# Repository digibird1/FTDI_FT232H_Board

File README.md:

FTDI_FT232H_Board
=================

PCB design for the FT232H USB 2.0 conroler chip. 
The design connects to the GPIO of the Altera DE0  FPGA board

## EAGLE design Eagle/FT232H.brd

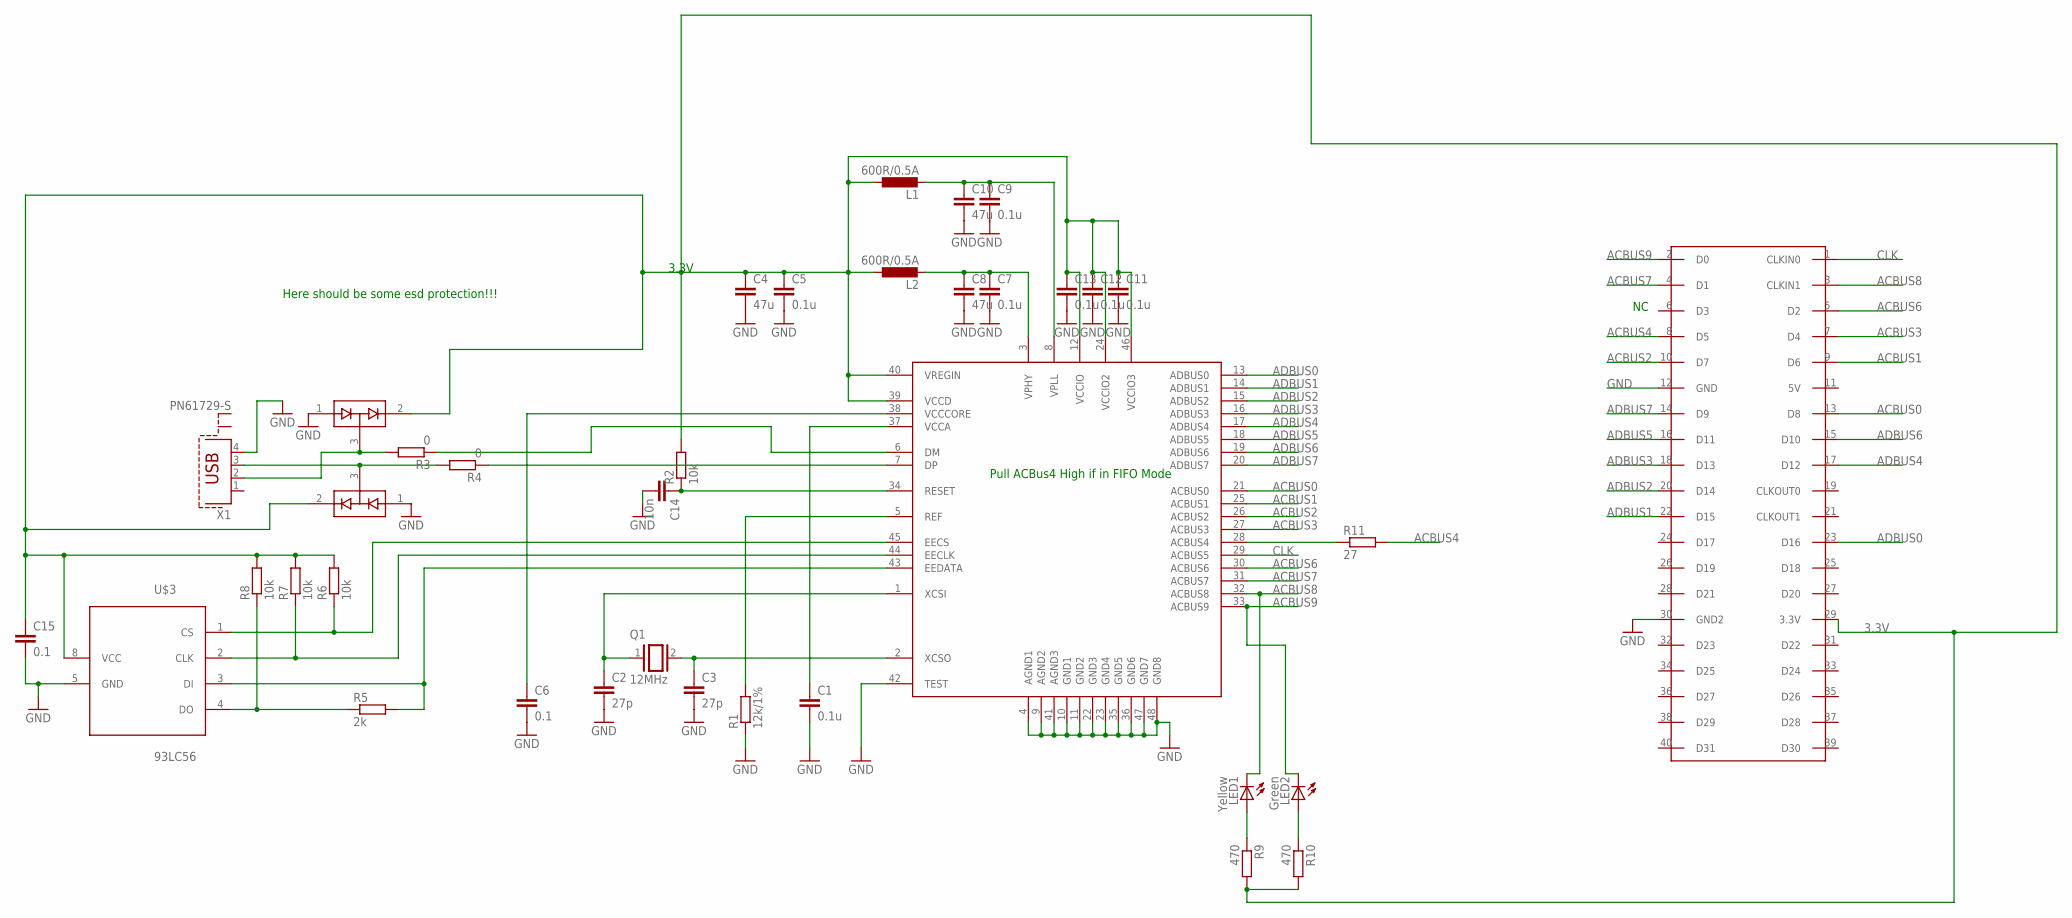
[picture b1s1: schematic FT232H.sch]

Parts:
C1, C5, C7, C9, C11, C12, C13: 0.1u; C0805
C2, C3: 27p; C0805
C4, C8, C10: 47u; C0805
C6, C15: 0.1; C0805
C14: 10n; C0805
D1, D2: BAV99; SOT23
L1, L2: 600R/0.5A; R0805
LED1: Yellow; R0805
LED2: Green; R0805
Q1: 12MHz; QS
R1: 12k/1%; M0805
R2, R6, R7, R8: 10k; M0805
R3, R4: 0; M0805
R5: 2k; M0805
R9, R10: 470; M0805
R11: 27; M0805
U$1: FT232H; LQFP48
U$2: FPGA_GPIO_DE0; 2X20
U$3: 93LC56; DIL-08
X1: PN61729-S

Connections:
3.3V: C4.1, C5.1, C11.1, C12.1, C13.1, C15.1, D1.2 (C2), D2.2 (C2), L1.1, L2.1, R2.2, R6.2, R7.2, R8.2, R9.2, R10.2, U$1.12 (VCCIO), U$1.24 (VCCIO2), U$1.39 (VCCD), U$1.40 (VREGIN), U$1.46 (VCCIO3), U$2.29 (3.3V), U$3.8 (VCC)
ACBUS0: U$1.21 (ACBUS0), U$2.13 (D8)
ACBUS1: U$1.25 (ACBUS1), U$2.9 (D6)
ACBUS2: U$1.26 (ACBUS2), U$2.10 (D7)
ACBUS3: U$1.27 (ACBUS3), U$2.7 (D4)
ACBUS4: R11.2, U$2.8 (D5)
ACBUS6: U$1.30 (ACBUS6), U$2.5 (D2)
ACBUS7: U$1.31 (ACBUS7), U$2.4 (D1)
ACBUS8: LED1.2 (C), U$1.32 (ACBUS8), U$2.3 (CLKIN1)
ACBUS9: LED2.2 (C), U$1.33 (ACBUS9), U$2.2 (D0)
ADBUS0: U$1.13 (ADBUS0), U$2.23 (D16)
ADBUS1: U$1.14 (ADBUS1), U$2.22 (D15)
ADBUS2: U$1.15 (ADBUS2), U$2.20 (D14)
ADBUS3: U$1.16 (ADBUS3), U$2.18 (D13)
ADBUS4: U$1.17 (ADBUS4), U$2.17 (D12)
ADBUS5: U$1.18 (ADBUS5), U$2.16 (D11)
ADBUS6: U$1.19 (ADBUS6), U$2.15 (D10)
ADBUS7: U$1.20 (ADBUS7), U$2.14 (D9)
CLK: U$1.29 (ACBUS5), U$2.1 (CLKIN0)
GND: C1.2, C2.2, C3.2, C4.2, C5.2, C6.2, C7.2, C8.2, C9.2, C10.2, C11.2, C12.2, C13.2, C14.2, C15.2, D1.1 (A1), D2.1 (A1), R1.1, U$1.4 (AGND1), U$1.9 (AGND2), U$1.10 (GND1), U$1.11 (GND2), U$1.22 (GND3), U$1.23 (GND4), U$1.35 (GND5), U$1.36 (GND6), U$1.41 (AGND3), U$1.42 (TEST), U$1.47 (GND7), U$1.48 (GND8), U$2.12 (GND), U$2.30 (GND2), U$3.5 (GND), X1.4
unnamed: C9.1, C10.1, L1.2, U$1.8 (VPLL)
unnamed: C1.1, U$1.37 (VCCA)
unnamed: R1.2, U$1.5 (REF)
unnamed: C6.1, U$1.38 (VCCCORE)
unnamed: C2.1, Q1.1, U$1.1 (XCSI)
unnamed: C3.1, Q1.2, U$1.2 (XCSO)
unnamed: C14.1, R2.1, U$1.34 (RESET)
unnamed: R4.1, U$1.7 (DP)
unnamed: D1.3 (COM), R3.2, X1.2
unnamed: R3.1, U$1.6 (DM)
unnamed: C7.1, C8.1, L2.2, U$1.3 (VPHY)
unnamed: D2.3 (COM), R4.2, X1.3
unnamed: R6.1, U$1.45 (EECS), U$3.1 (CS)
unnamed: R7.1, U$1.44 (EECLK), U$3.2 (CLK)
unnamed: R5.2, U$1.43 (EEDATA), U$3.3 (DI)
unnamed: R5.1, R8.1, U$3.4 (DO)
unnamed: LED1.1 (A), R9.1
unnamed: LED2.1 (A), R10.1
unnamed: R11.1, U$1.28 (ACBUS4)

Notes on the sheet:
3.3V
Here should be some esd protection!!!
Pull ACBus4 High if in FIFO Mode

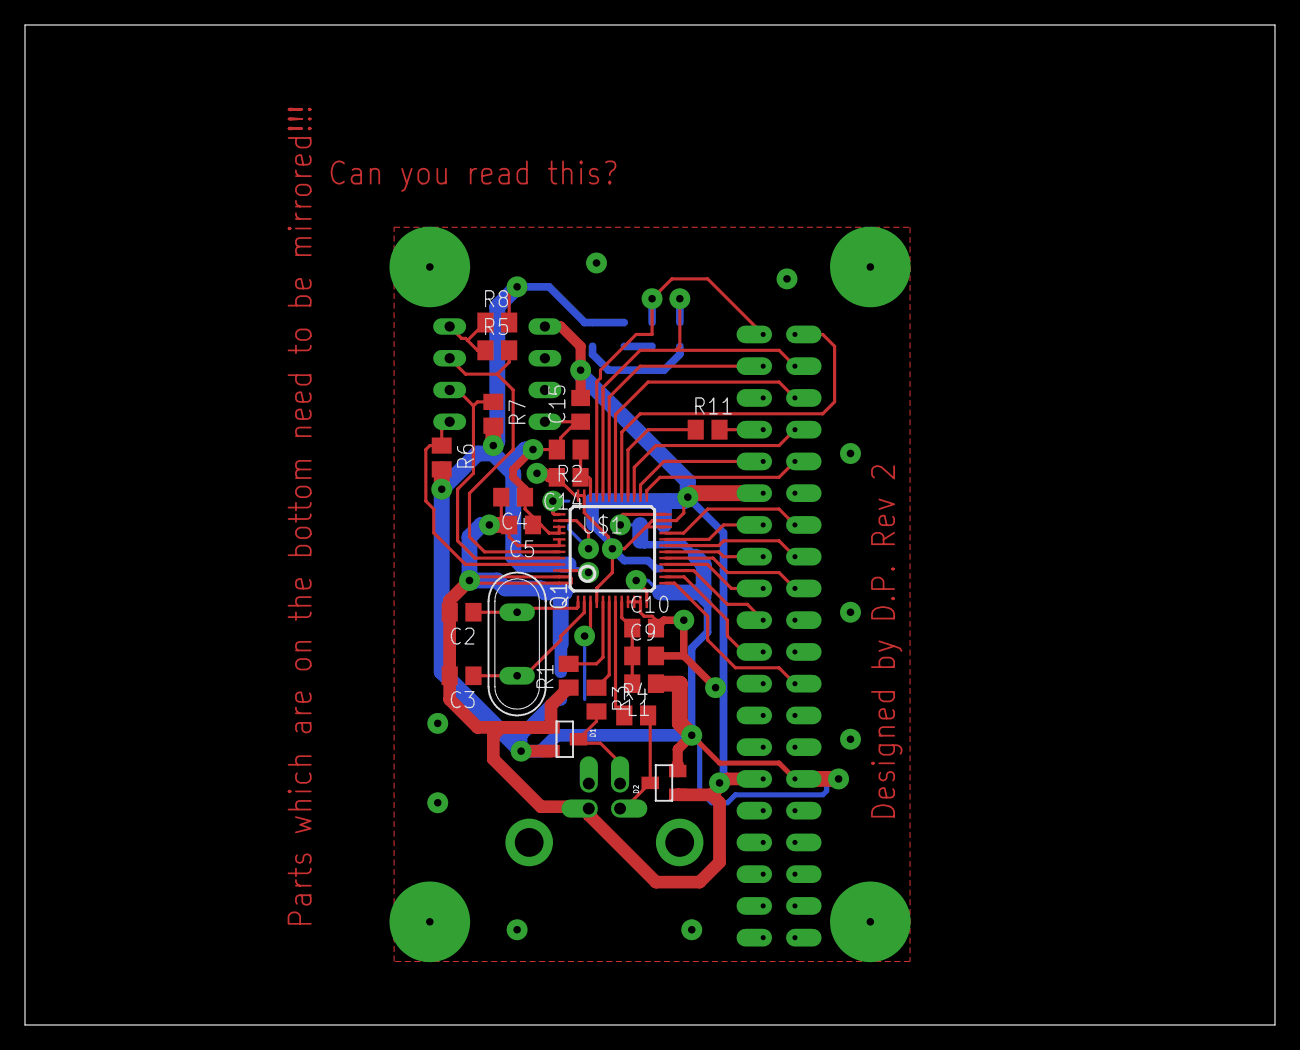
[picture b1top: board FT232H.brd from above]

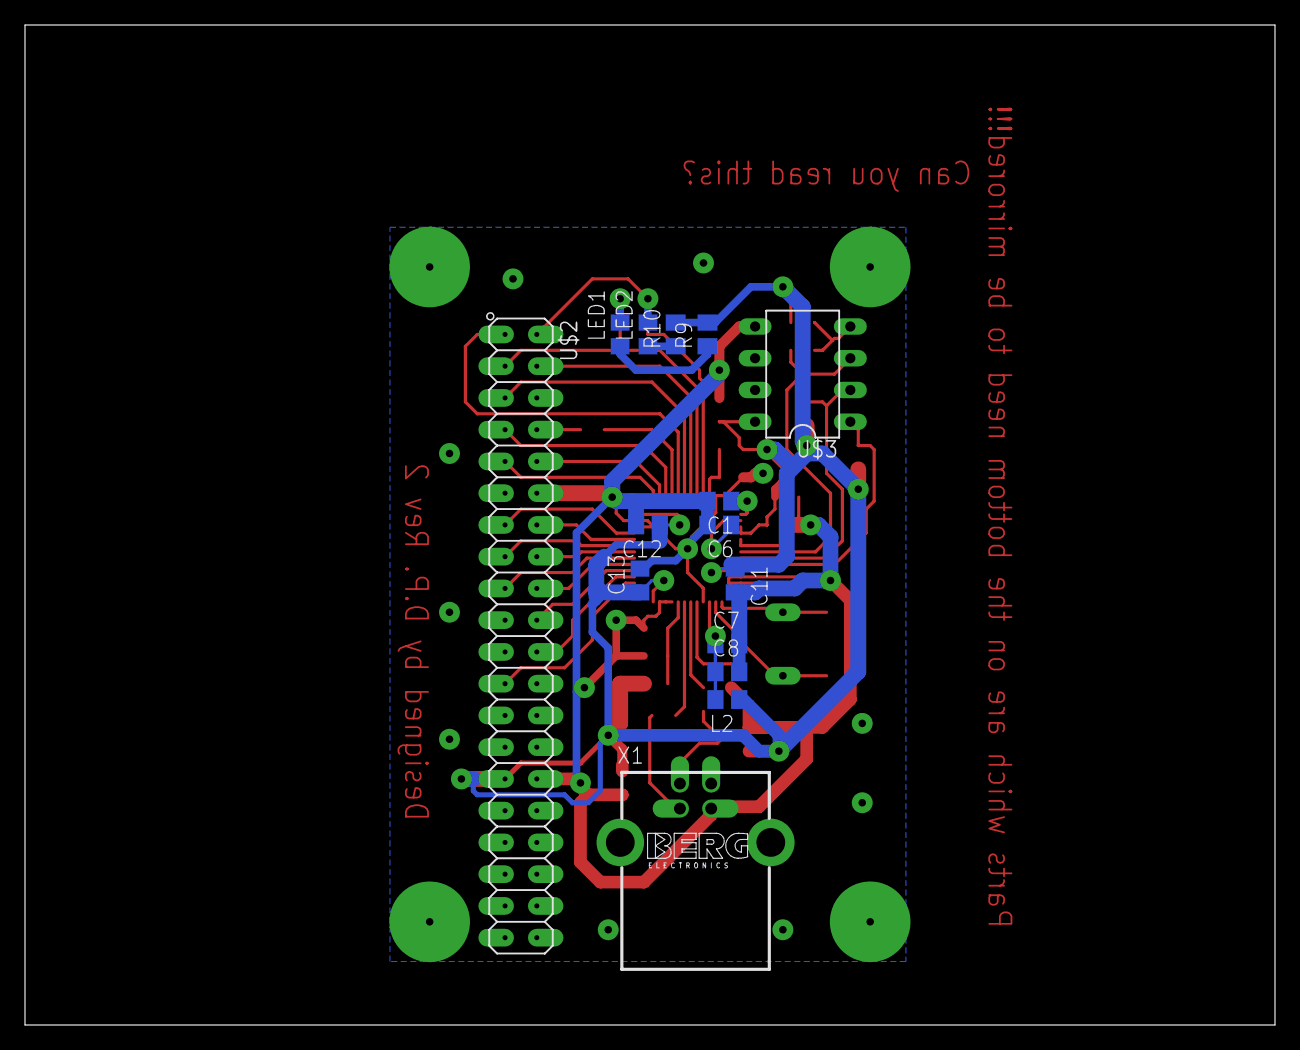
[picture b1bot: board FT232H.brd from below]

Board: 2 copper layers, 100.0 x 80.0 mm, 37 parts (15 on the bottom side), 39 nets.

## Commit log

2014-12-29 Import the Eagle Files
